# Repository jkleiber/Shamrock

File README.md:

# six-wheel-robot
Hardware development for a six wheel mobile robot

### Folders
* Electrical
  * Contains some schematics for future electrical designs. Currently a very early work-in-progress.
* Mechanical
  * Full 3D CAD model of the robot using Autodesk Inventor
  
### Pictures

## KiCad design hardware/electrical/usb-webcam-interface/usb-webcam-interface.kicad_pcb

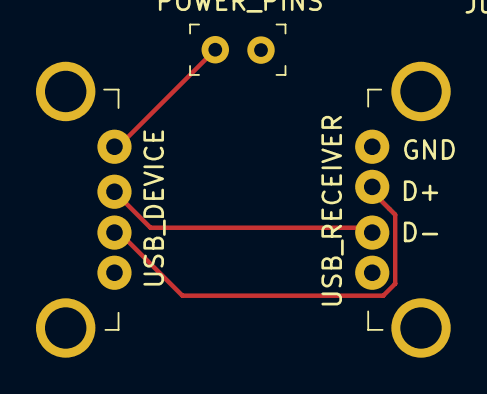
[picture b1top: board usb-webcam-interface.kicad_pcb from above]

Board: 2 copper layers, 3 parts (0 on the bottom side), 4 nets.

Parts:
POWER_PINS: M20-9990246; PinHeader_1x2_P2.54mm
USB_DEVICE: UE27AC54100; USB_A_Female_UE27AC54100
USB_RECEIVER: UE27AC54100; USB_A_Female_UE27AC54100

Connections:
GND: POWER_PINS.2, USB_DEVICE.4, USB_RECEIVER.4
unnamed: POWER_PINS.1, USB_DEVICE.1
unnamed: USB_DEVICE.2, USB_RECEIVER.2
unnamed: USB_DEVICE.3, USB_RECEIVER.3

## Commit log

2018-07-29 Adds initial hardware design concept and begins work on the electronics assembly
2018-07-30 Attaches the Arduino, Raspberry Pi 3 B+, and the L298N motor controller
2019-05-07 Electronics layer fully drafted. Ready to 3D print and cut the next iteration
2019-05-07 Updated assembly...
2019-06-22 Makes initial ROS workspace Adds driving test, which works on the robot. This will help with future configuration
2019-07-14 Reorganizes the hardware section and creates a PCB for the webcam
2019-07-28 Makes initial project for drivetrain schematic.
    Adds tests for encoders, including tracking loop for velocity estimates
2019-07-28 Makes tracking loop work for estimating velocity
    need to fix a hack and add acceleration
2019-07-28 Adds robotlib as a reference in this repo
2019-07-28 removes g-code from project
2019-07-28 Removes random HTML file
2019-07-28 Makes tracking loop work without hack
    About to explore velocity + accel tracking, and filtering of output for feedback
2019-07-28 Tracks robotlib improvements
2019-07-28 Implements a tracking loop for measuring encoder velocity, adds it to robotlib
2019-08-09 Begins software and firmware development, IMU integration, and kalman filter design
2019-08-09 Adds kalman filter design docs to repo
2020-01-23 Begins work on implementing the EKF
2020-06-13 Focuses repo on hardware development. Will make another repo for software development
    Goal of software development repo will be to be more general for wide range of robots using docker and ROS2
2020-06-13 Adds picture of robot to the README
2020-06-13 Gets picture to display in readme
